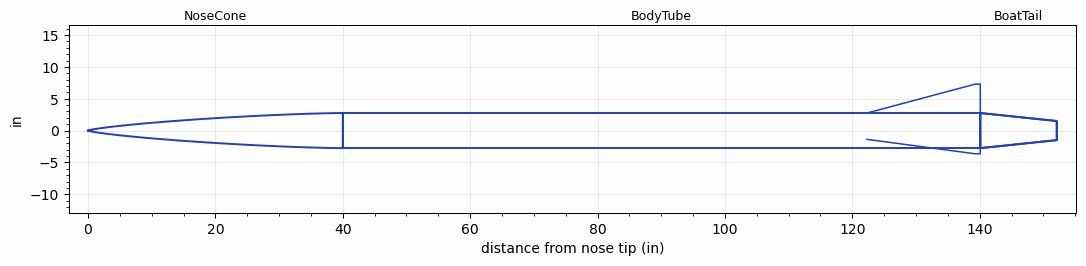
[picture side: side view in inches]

<RASAeroDocument>
 <FileVersion>2</FileVersion>
 <RocketDesign>
  <NoseCone>
   <Length>40</Length>
   <Diameter>5.51</Diameter>
   <Shape>Von Karman Ogive</Shape>
   <Location>0</Location>
  </NoseCone>
  <BodyTube>
   <Length>100.1</Length>
   <Diameter>5.51</Diameter>
   <Location>40</Location>
   <BoattailLength>12</BoattailLength>
   <BoattailRearDiameter>3</BoattailRearDiameter>
   <Fin>
    <Count>3</Count>
    <Chord>17.8</Chord>
    <Span>4.54</Span>
    <SweepDistance>17</SweepDistance>
    <TipChord>0.79</TipChord>
    <Thickness>0.1968</Thickness>
    <Location>17.8</Location>
    <AirfoilSection>Hexagonal</AirfoilSection>
    <FX1>1</FX1>
    <FX3>1</FX3>
   </Fin>
  </BodyTube>
  <BoatTail>
   <Length>12</Length>
   <Diameter>5.51</Diameter>
   <RearDiameter>3</RearDiameter>
   <Location>140.1</Location>
  </BoatTail>
  <Surface>Camouflage Paint</Surface>
  <ModifiedBarrowman>False</ModifiedBarrowman>
  <Turbulence>True</Turbulence>
  <UseBooster1>False</UseBooster1>
  <UseBooster2>False</UseBooster2>
 </RocketDesign>
 <LaunchSite>
  <Altitude>0</Altitude>
  <Pressure>0</Pressure>
  <RodAngle>3</RodAngle>
  <RodLength>6.6</RodLength>
  <Temperature>74</Temperature>
  <WindSpeed>6</WindSpeed>
 </LaunchSite>
 <Recovery>
  <Altitude1>1000</Altitude1>
  <Altitude2>1000</Altitude2>
  <DeviceType1>None</DeviceType1>
  <DeviceType2>None</DeviceType2>
  <Event1>False</Event1>
  <Event2>False</Event2>
  <Size1>1</Size1>
  <Size2>1</Size2>
  <EventType1>None</EventType1>
  <EventType2>None</EventType2>
  <CD1>1.33</CD1>
  <CD2>1.33</CD2>
 </Recovery>
 <SimulationList>
  <Simulation>
   <SustainerEngine>O3400-IM-P  (CTI)</SustainerEngine>
   <SustainerLaunchWt>59.5</SustainerLaunchWt>
   <SustainerNozzleDiameter>3.8</SustainerNozzleDiameter>
   <SustainerCG>70</SustainerCG>
   <SustainerIgnitionDelay>0</SustainerIgnitionDelay>
   <Booster1SeparationDelay>0</Booster1SeparationDelay>
   <Booster1IgnitionDelay>0</Booster1IgnitionDelay>
   <IncludeBooster1>False</IncludeBooster1>
   <Booster2Delay>0</Booster2Delay>
   <IncludeBooster2>False</IncludeBooster2>
   <TimetoApogee>46.06828</TimetoApogee>
   <MaxAltitude>43979.1</MaxAltitude>
   <MaxVelocity>2630.4</MaxVelocity>
   <OptimumWt>41.77812</OptimumWt>
   <OptimumMaxAlt>41.77812</OptimumMaxAlt>
  </Simulation>
  <Simulation>
   <SustainerEngine>N2540-GR-P  (CTI)</SustainerEngine>
   <SustainerLaunchWt>46</SustainerLaunchWt>
   <SustainerNozzleDiameter>3.85</SustainerNozzleDiameter>
   <SustainerCG>1</SustainerCG>
   <SustainerIgnitionDelay>0</SustainerIgnitionDelay>
   <Booster1SeparationDelay>0</Booster1SeparationDelay>
   <Booster1IgnitionDelay>0</Booster1IgnitionDelay>
   <IncludeBooster1>False</IncludeBooster1>
   <Booster2Delay>0</Booster2Delay>
   <IncludeBooster2>False</IncludeBooster2>
   <TimetoApogee>40.46922</TimetoApogee>
   <MaxAltitude>37012.63</MaxAltitude>
   <MaxVelocity>2861.462</MaxVelocity>
   <OptimumWt>41.6875</OptimumWt>
   <OptimumMaxAlt>41.6875</OptimumMaxAlt>
  </Simulation>
 </SimulationList>
</RASAeroDocument>
